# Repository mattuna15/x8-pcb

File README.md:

Commander X8 PCB
================

This repository contains the PCB design of the Commander X8.

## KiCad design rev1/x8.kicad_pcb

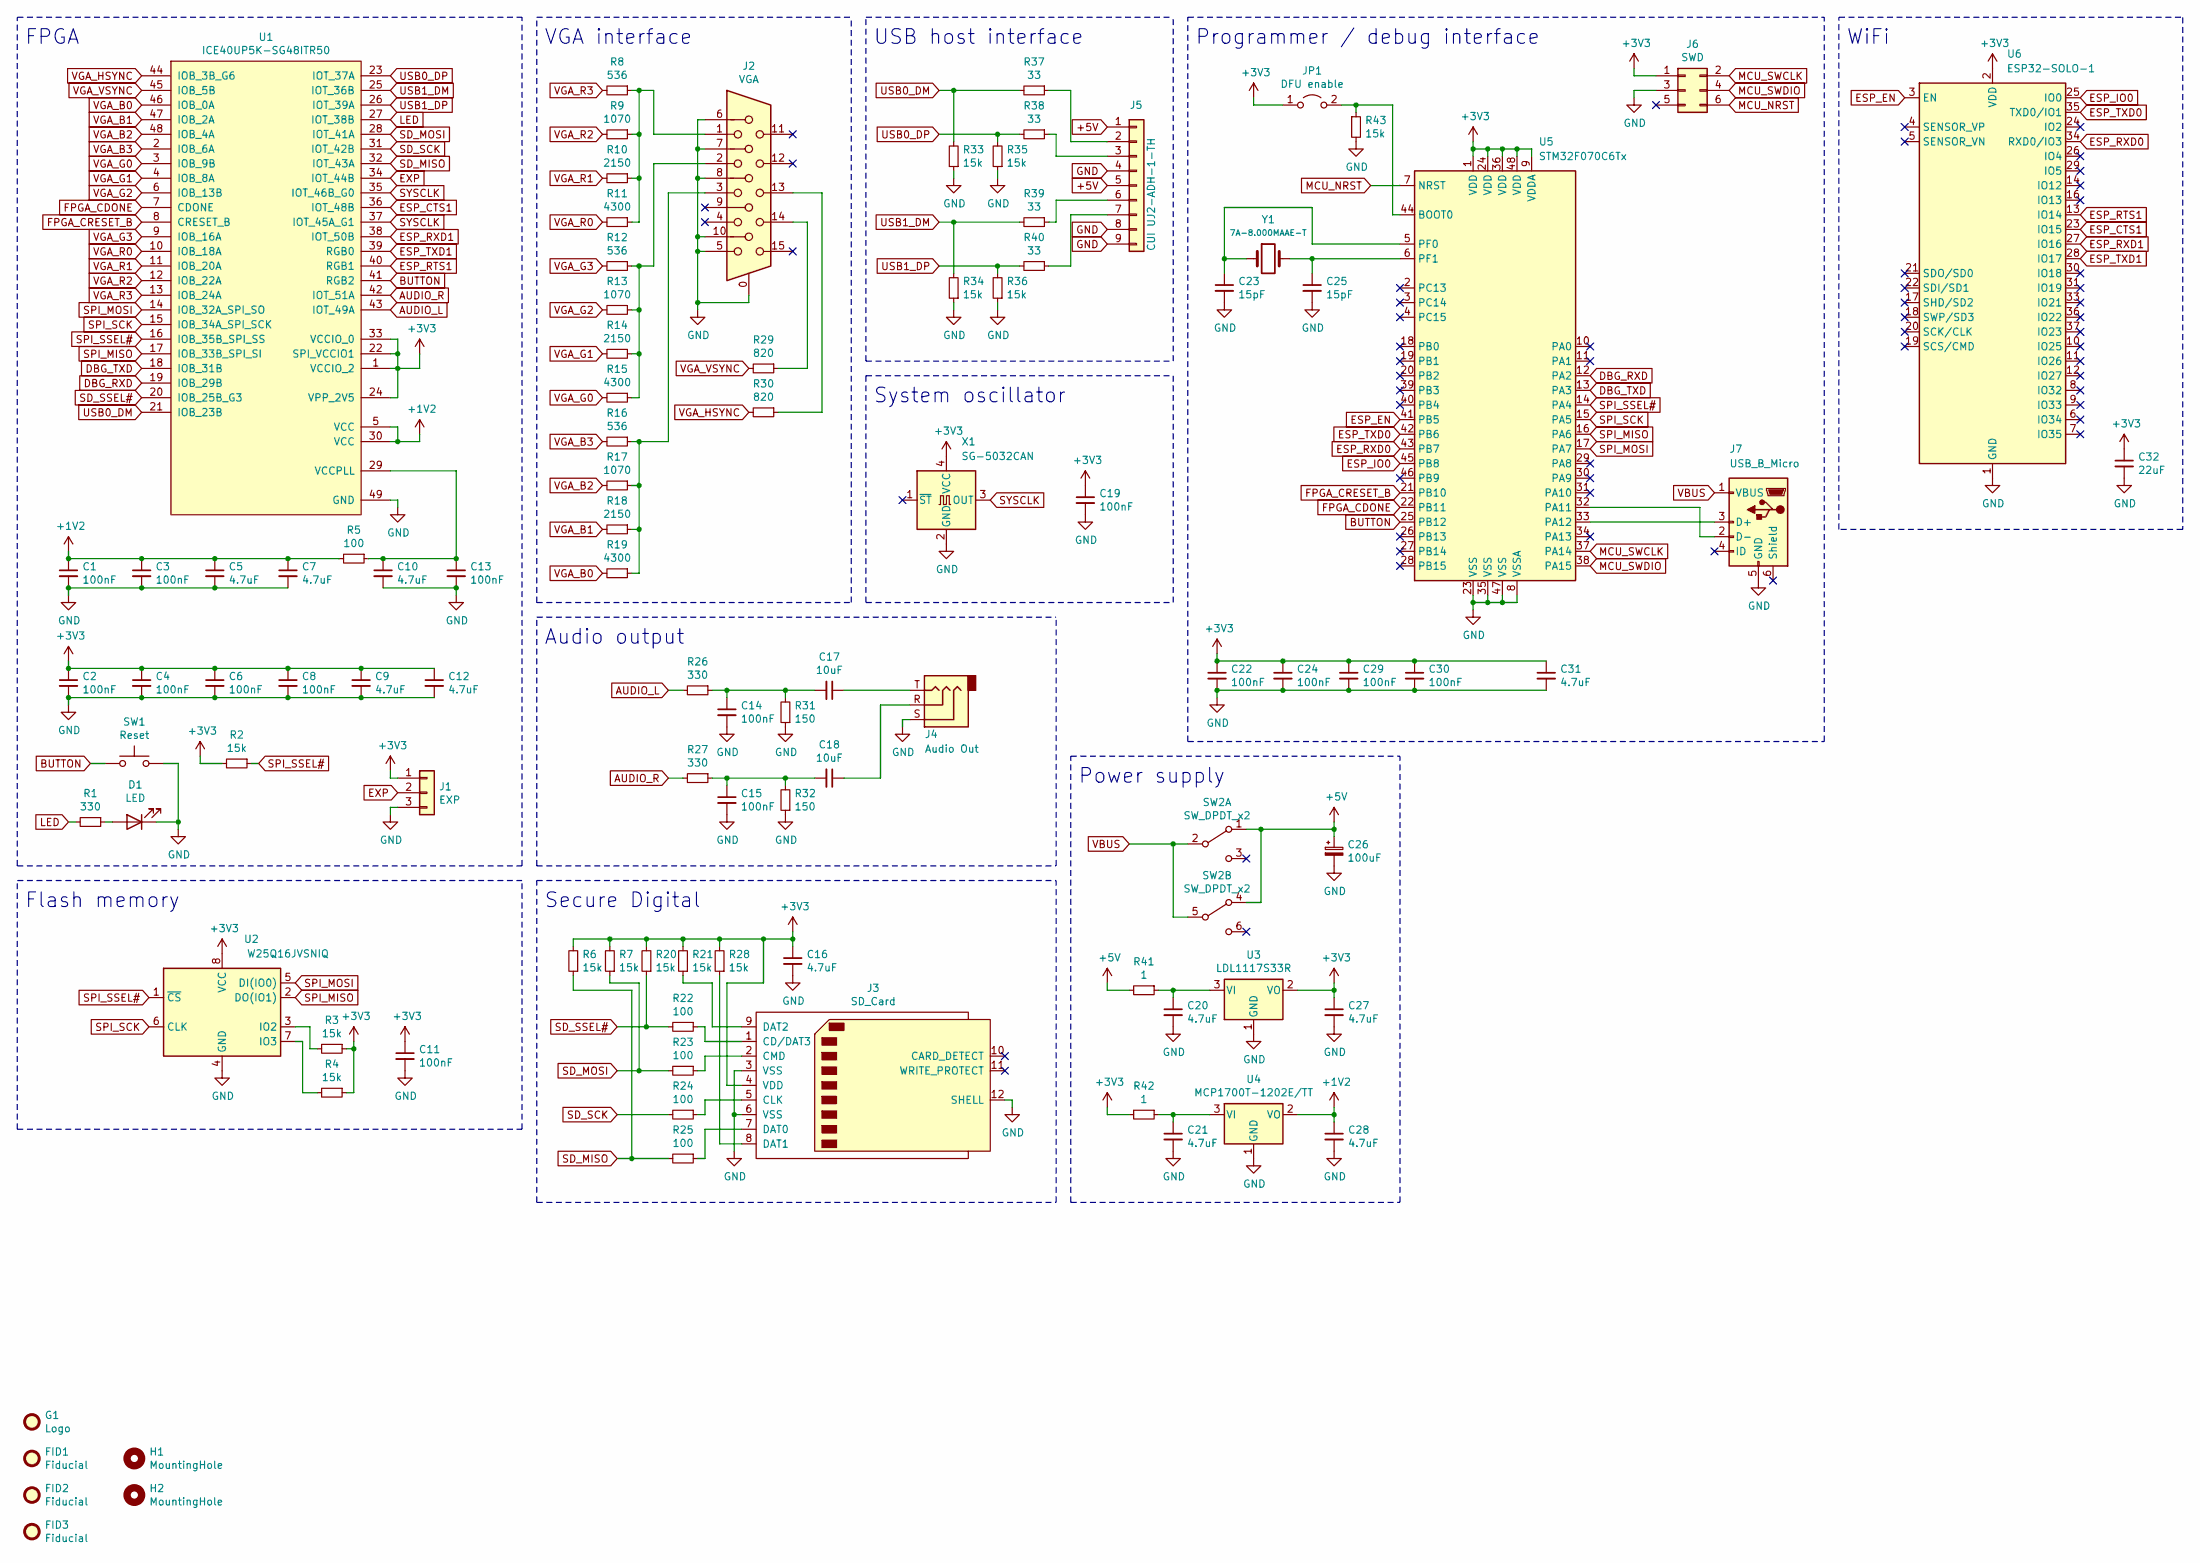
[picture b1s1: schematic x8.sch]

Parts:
C1, C2, C3, C4, C6, C8, C11, C13, C14, C15, C19, C22, C24, C29, C30: 100nF; C_0603_1608Metric
C5, C7, C9, C10, C12, C16, C20, C21, C27, C28, C31: 4.7uF; C_0603_1608Metric
C17, C18: 10uF; C_0805_2012Metric
C23, C25: 15pF; C_0603_1608Metric
C26: 100uF; CP_Elec_6.3x7.7
C32: 22uF; C_1206_3216Metric
D1: LED; LED_0603_1608Metric
FID1, FID2, FID3: Fiducial; Fiducial_1mm_Mask2mm
G1: Logo; logo
H1, H2: MountingHole; MountingHole_3.2mm_M3
J1: EXP; PinHeader_1x03_P2.54mm_Vertical
J2: VGA; ICD15S13E4GV00LF
J3: SD_Card; SD_TE_2041021
J4: Audio Out; Jack_3.5mm_CUI_SJ-3523-SMT_Horizontal
J5: CUI UJ2-ADH-1-TH; USB_A_Wuerth_61400826021_Horizontal_Stacked
J6: SWD; PinHeader_2x03_P2.54mm_Vertical
J7: USB_B_Micro; USB_Micro-B_Amphenol_10103594-0001LF_Horizontal
JP1: DFU enable; PinHeader_1x02_P2.54mm_Vertical
R1, R26, R27: 330; R_0603_1608Metric
R2, R3, R4, R6, R7, R20, R21, R28, R33, R34, R35, R36, R43: 15k; R_0603_1608Metric
R5, R22, R23, R24, R25: 100; R_0603_1608Metric
R8, R12, R16: 536; R_0603_1608Metric
R9, R13, R17: 1070; R_0603_1608Metric
R10, R14, R18: 2150; R_0603_1608Metric
R11, R15, R19: 4300; R_0603_1608Metric
R29, R30: 820; R_0603_1608Metric
R31, R32: 150; R_0603_1608Metric
R37, R38, R39, R40: 33; R_0603_1608Metric
R41, R42: 1; R_0603_1608Metric
SW1: Reset; SW_Tactile_SPST_Angled_PTS645Vx58-2LFS
SW2: SW_DPDT_x2; SW_E-Switch_EG2219_DPDT_Angled
U1: ICE40UP5K-SG48ITR50; QFN-48-1EP_7x7mm_P0.5mm_EP5.3x5.3mm
U2: W25Q16JVSNIQ; SOIC-8_3.9x4.9mm_P1.27mm
U3: LDL1117S33R; SOT-223-3_TabPin2
U4: MCP1700T-1202E/TT; SOT-23
U5: STM32F070C6Tx; LQFP-48_7x7mm_P0.5mm
U6: ESP32-SOLO-1; ESP32-WROOM-32
X1: SG-5032CAN; Oscillator_SMD_SeikoEpson_SG8002LB-4Pin_5.0x3.2mm
Y1: 7A-8.000MAAE-T; Crystal_SMD_TXC_7A-2Pin_5x3.2mm

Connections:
+1V2: C1.1, C3.1, C5.1, C7.1, C28.1, R5.2, U1.5 (VCC), U1.30 (VCC), U4.2 (VO)
+3V3: C2.1, C4.1, C6.1, C8.1, C9.1, C11.1, C12.1, C16.1, C19.1, C22.1, C24.1, C27.1, C29.1, C30.1, C31.1, C32.1, J1.1, J3.4 (VDD), J6.1, JP1.1 (A), R2.2, R3.1, R4.1, R6.2, R7.2, R20.2, R21.2, R28.2, R42.2, U1.1 (VCCIO_2), U1.22 (SPI_VCCIO1), U1.24 (VPP_2V5), U1.33 (VCCIO_0), U2.8 (VCC), U3.2 (VO), U5.1 (VDD), U5.9 (VDDA), U5.24 (VDD), U5.36 (VDD), U5.48 (VDD), U6.2 (VDD), X1.4 (VCC)
+5V: C26.1, J5.1, J5.5, R41.2, SW2.1 (A), SW2.4 (A)
AUDIO_L: R26.2, U1.43 (IOT_49A)
AUDIO_R: R27.2, U1.42 (IOT_51A)
BUTTON: SW1.1, U1.41 (RGB2), U5.25 (PB12)
DBG_RXD: U1.19 (IOB_29B), U5.12 (PA2)
DBG_TXD: U1.18 (IOB_31B), U5.13 (PA3)
ESP_CTS1: U1.36 (IOT_48B), U6.23 (IO15)
ESP_EN: U5.41 (PB5), U6.3 (EN)
ESP_IO0: U5.45 (PB8), U6.25 (IO0)
ESP_RTS1: U1.40 (RGB1), U6.13 (IO14)
ESP_RXD0: U5.43 (PB7), U6.34 (RXD0/IO3)
ESP_RXD1: U1.38 (IOT_50B), U6.27 (IO16)
ESP_TXD0: U5.42 (PB6), U6.35 (TXD0/IO1)
ESP_TXD1: U1.39 (RGB0), U6.28 (IO17)
EXP: J1.2, U1.34 (IOT_44B)
FPGA_CDONE: U1.7 (CDONE), U5.22 (PB11)
FPGA_CRESET_B: U1.8 (CRESET_B), U5.21 (PB10)
GND: C1.2, C2.2, C3.2, C4.2, C5.2, C6.2, C7.2, C8.2, C9.2, C10.2, C11.2, C12.2, C13.2, C14.2, C15.2, C16.2, C19.2, C20.2, C21.2, C22.2, C23.2, C24.2, C25.2, C26.2, C27.2, C28.2, C29.2, C30.2, C31.2, C32.2, D1.1 (K), J1.3, J2.0, J2.5, J2.6, J2.7, J2.8, J2.10, J3.3 (VSS), J3.6 (VSS), J3.12 (SHELL), J4.S, J5.4, J5.8, J5.9, J6.3, J7.5 (GND), R31.1, R32.1, R33.1, R34.1, R35.1, R36.1, R43.2, SW1.2, U1.49 (GND), U2.4 (GND), U3.1 (GND), U4.1 (GND), U5.8 (VSSA), U5.23 (VSS), U5.35 (VSS), U5.47 (VSS), U6.1 (GND), U6.15 (GND), U6.38 (GND), U6.39 (GND), X1.2 (GND)
LED: R1.2, U1.27 (IOT_38B)
MCU_NRST: J6.6, U5.7 (NRST)
MCU_SWCLK: J6.2, U5.37 (PA14)
MCU_SWDIO: J6.4, U5.38 (PA15)
unnamed: C10.1, C13.1, R5.1, U1.29 (VCCPLL)
unnamed: C14.1, C17.2, R26.1, R31.2
unnamed: C15.1, C18.2, R27.1, R32.2
unnamed: C17.1, J4.T
unnamed: C18.1, J4.R
unnamed: C20.1, R41.1, U3.3 (VI)
unnamed: C21.1, R42.1, U4.3 (VI)
unnamed: C23.1, U5.5 (PF0), Y1.1
unnamed: C25.1, U5.6 (PF1), Y1.2
unnamed: D1.2 (A), R1.1
unnamed: J2.1, R8.1, R9.1, R10.1, R11.1
unnamed: J2.2, R12.1, R13.1, R14.1, R15.1
unnamed: J2.3, R16.1, R17.1, R18.1, R19.1
unnamed: J2.13, R30.1
unnamed: J2.14, R29.1
unnamed: J3.1 (CD/DAT3), R22.1
unnamed: J3.2 (CMD), R23.1
unnamed: J3.5 (CLK), R24.1
unnamed: J3.7 (DAT0), R25.1
unnamed: J3.8 (DAT1), R28.1
unnamed: J3.9 (DAT2), R21.1
unnamed: J5.2, R37.1
unnamed: J5.3, R38.1
unnamed: J5.6, R39.1
unnamed: J5.7, R40.1
unnamed: J7.2 (D-), U5.32 (PA11)
unnamed: J7.3 (D+), U5.33 (PA12)
unnamed: JP1.2 (B), R43.1, U5.44 (BOOT0)
unnamed: R3.2, U2.3 (IO2)
unnamed: R4.2, U2.7 (IO3)
SD_MISO: R6.1, R25.2, U1.32 (IOT_43A)
SD_MOSI: R7.1, R23.2, U1.28 (IOT_41A)
SD_SCK: R24.2, U1.31 (IOT_42B)
SD_SSEL#: R20.1, R22.2, U1.20 (IOB_25B_G3)
SPI_MISO: U1.17 (IOB_33B_SPI_SI), U2.2 (DO(IO1)), U5.16 (PA6)
SPI_MOSI: U1.14 (IOB_32A_SPI_SO), U2.5 (DI(IO0)), U5.17 (PA7)
SPI_SCK: U1.15 (IOB_34A_SPI_SCK), U2.6 (CLK), U5.15 (PA5)
SPI_SSEL#: R2.1, U1.16 (IOB_35B_SPI_SS), U2.1 (~CS), U5.14 (PA4)
SYSCLK: U1.35 (IOT_46B_G0), U1.37 (IOT_45A_G1), X1.3 (OUT)
USB0_DM: R33.2, R37.2, U1.21 (IOB_23B)
USB0_DP: R35.2, R38.2, U1.23 (IOT_37A)
USB1_DM: R34.2, R39.2, U1.25 (IOT_36B)
USB1_DP: R36.2, R40.2, U1.26 (IOT_39A)
VBUS: J7.1 (VBUS), SW2.2 (B), SW2.5 (B)
VGA_B0: R19.2, U1.46 (IOB_0A)
VGA_B1: R18.2, U1.47 (IOB_2A)
VGA_B2: R17.2, U1.48 (IOB_4A)
VGA_B3: R16.2, U1.2 (IOB_6A)
VGA_G0: R15.2, U1.3 (IOB_9B)
VGA_G1: R14.2, U1.4 (IOB_8A)
VGA_G2: R13.2, U1.6 (IOB_13B)
VGA_G3: R12.2, U1.9 (IOB_16A)
VGA_HSYNC: R30.2, U1.44 (IOB_3B_G6)
VGA_R0: R11.2, U1.10 (IOB_18A)
VGA_R1: R10.2, U1.11 (IOB_20A)
VGA_R2: R9.2, U1.12 (IOB_22A)
VGA_R3: R8.2, U1.13 (IOB_24A)
VGA_VSYNC: R29.2, U1.45 (IOB_5B)

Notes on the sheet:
VGA interface
FPGA
USB host interface
Power supply
Audio output
WiFi
Flash memory
System oscillator
Programmer / debug interface
Secure Digital

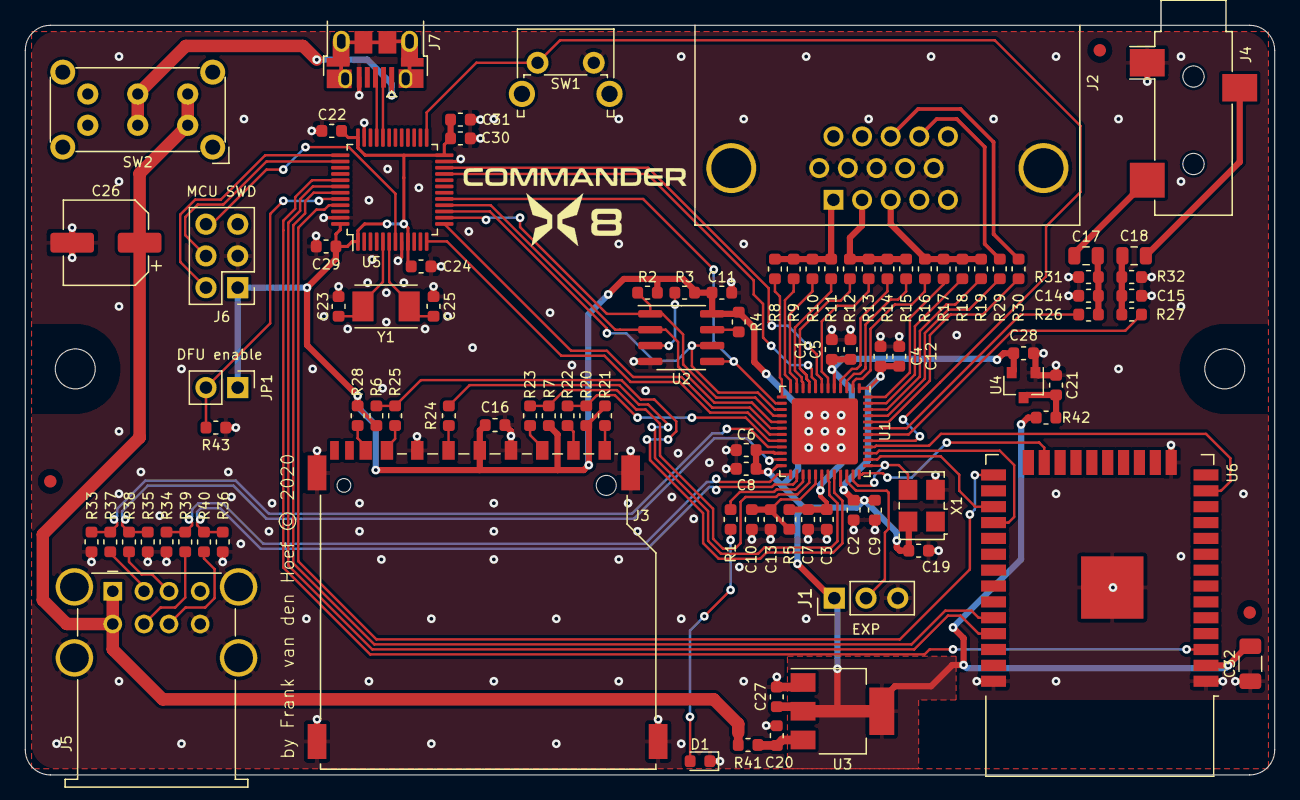
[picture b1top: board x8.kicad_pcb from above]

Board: 2 copper layers, 100.0 x 60.0 mm, 100 parts (0 on the bottom side), 82 nets.

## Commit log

2020-12-26 Initial commit.
2020-12-26 Added README.

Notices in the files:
rev1/x8.kicad_pcb:
by Frank van den Hoef © 2020
rev1/x8.sch:
Copyright (C) 2020 Frank van den Hoef, License: 2-clause BSD
